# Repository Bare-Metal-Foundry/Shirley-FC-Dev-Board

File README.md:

<!--
This project follows atomic documentation.
Each subsystem is documented independently.
All configs are stored in YAML.
-->

# Shirley - Flight Controller Development Board

Shirley is high-performance flight controller hardware platform built around the STM32H743 microcontroller, designed for custom firmware development and compatibility with existing flight stacks.

## Features

### Core Hardware
- **MCU**: STM32H743ZIT6 (480 MHz Cortex-M7, FPU, DSP)
- **IMU**: ICM-40609-D (6-axis, low-noise, up to 32 kHz ODR)
- **Magnetometer**: MMC5983MA (18-bit precision with degaussing)
- **Barometer**: BMP390 High-precision altitude sensing
- **Storage**: SD card socket for flight data logging

### Power System
- **Input**: 5V via standard Pixhawk power module
- **Architecture**: 5V MUX + Dual 3.3V rails (digital + filtered analog) for low-noise sensor operation
- **Protection**: ESD protection on USB-C and power connector

### Connectivity
- **Motor Control**: 4x ESC outputs
- **RC Input**: Standard RC receiver connection
- **GPS**: Dedicated UART interface
- **Telemetry**: Bidirectional radio module support
- **USB**: Full-speed OTG for configuration and debugging
- **CAN**: FDCAN interface (in the GPS connector)
- **Debug**: Tag-Connect SWD/SWO interface

Note: All connectors are GH1.25 connectors

## Documentation

This project uses atomic documentation - each subsystem is documented independently in `/docs`:

- **[Hardware Overview](docs/hardware/overview.md)** - System architecture and block diagrams
- **[Power Architecture](docs/hardware/power-architecture.md)** - Power rail design and specifications
- **[Design Decisions](docs/hardware/design-decisions.md)** - Component selection rationale
- **[STM32 Subsystem](docs/hardware/stm32-subsystem/)** - MCU peripheral configuration

All hardware configurations are defined in machine-readable YAML format in `/config`:
- **[pinout.yaml](config/pinout.yaml)** - Complete STM32H743 pin assignments
- **[power.yaml](config/power.yaml)** - Power rail specifications and architecture

## Repository Structure

```
├── hardware/KiCad/FC_v1.0/         # KiCad 9.0 schematics and PCB layout
├── firmware/STM32 Cube IDE/        # STM32CubeMX configuration
├── config/                         # YAML configuration files
├── docs/                           # Atomic documentation by subsystem
├── docs/hardware/exports/          # exports and version history
└── resources/datasheets/           # Component datasheets organized by type
```

## Getting Started

### Overview
1. Exported schematics and renders can be found here: `exports/`
2. The different versions designed and produced are detailed here: `exports/versions-history.md`
3. An overview of the design can be found here: `docs/hardware/overview.md`

### Hardware Design
1. Open schematics in **KiCad 9.0**: `hardware/KiCad/FC_v1.0/FC-proto.kicad_sch`
2. Review hierarchical subsystem sheets (power, interfaces, sensors)
3. Custom component footprints are in `hardware/cad-layout/`

### Firmware Development
1. Open STM32CubeMX project: `firmware/STM32 Cube IDE/FC-proto-El.ioc`
2. Pin assignments match `config/pinout.yaml`
3. Connect debugger via Tag-Connect cable (SWD: PA13/PA14, SWO: PB3)

## Design Philosophy

This first revision prototype prioritizes:
- **Development-friendly**: Easy debugging via Tag-Connect, USB, and comprehensive logging
- **Compact Board**: Compact board to fit in smaller frames
- **Signal quality**: Low-noise analog power domain for sensor accuracy
- **Integration**: Integration with existing pixhawk drone hardware

## Flight Stack Compatibility

The hardware pinout and peripheral configuration supports:
- **PX4** - Full feature compatibility
- **Ardupilot** - Standard Pixhawk interface support
- **Betaflight** - High-rate control loop capability

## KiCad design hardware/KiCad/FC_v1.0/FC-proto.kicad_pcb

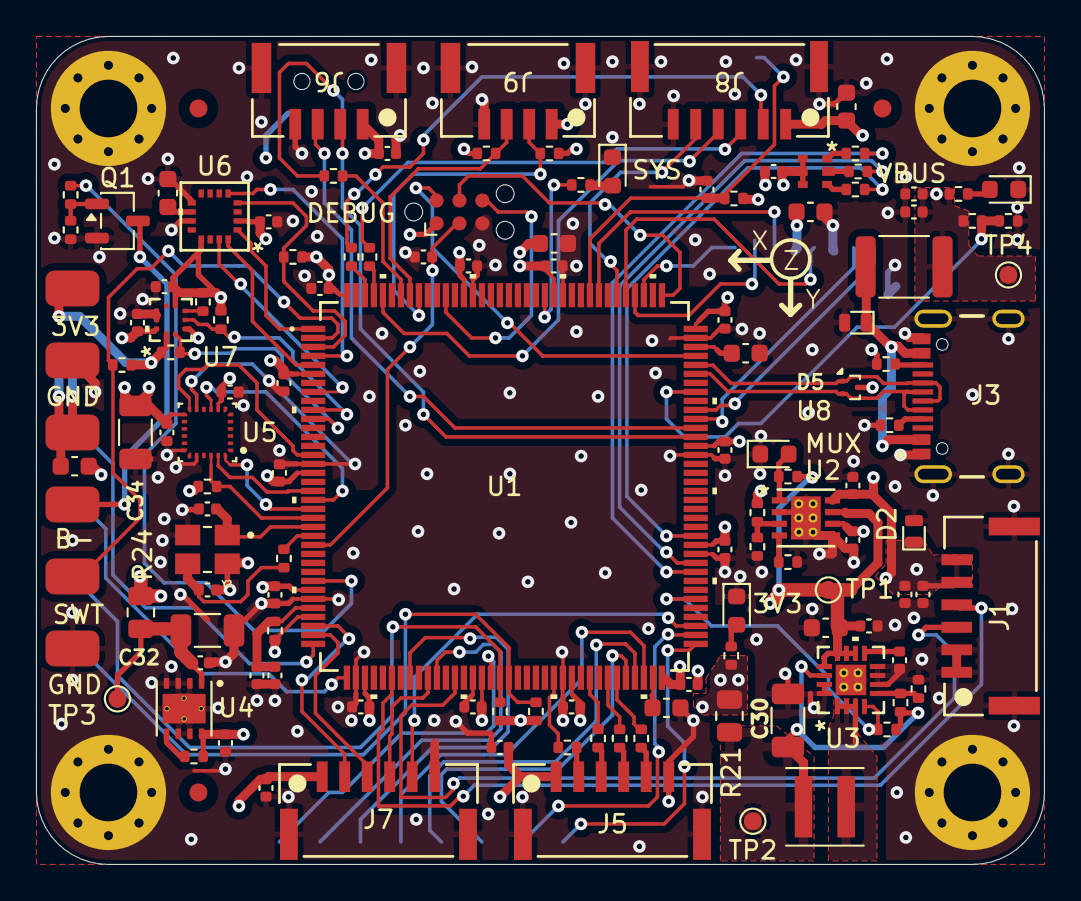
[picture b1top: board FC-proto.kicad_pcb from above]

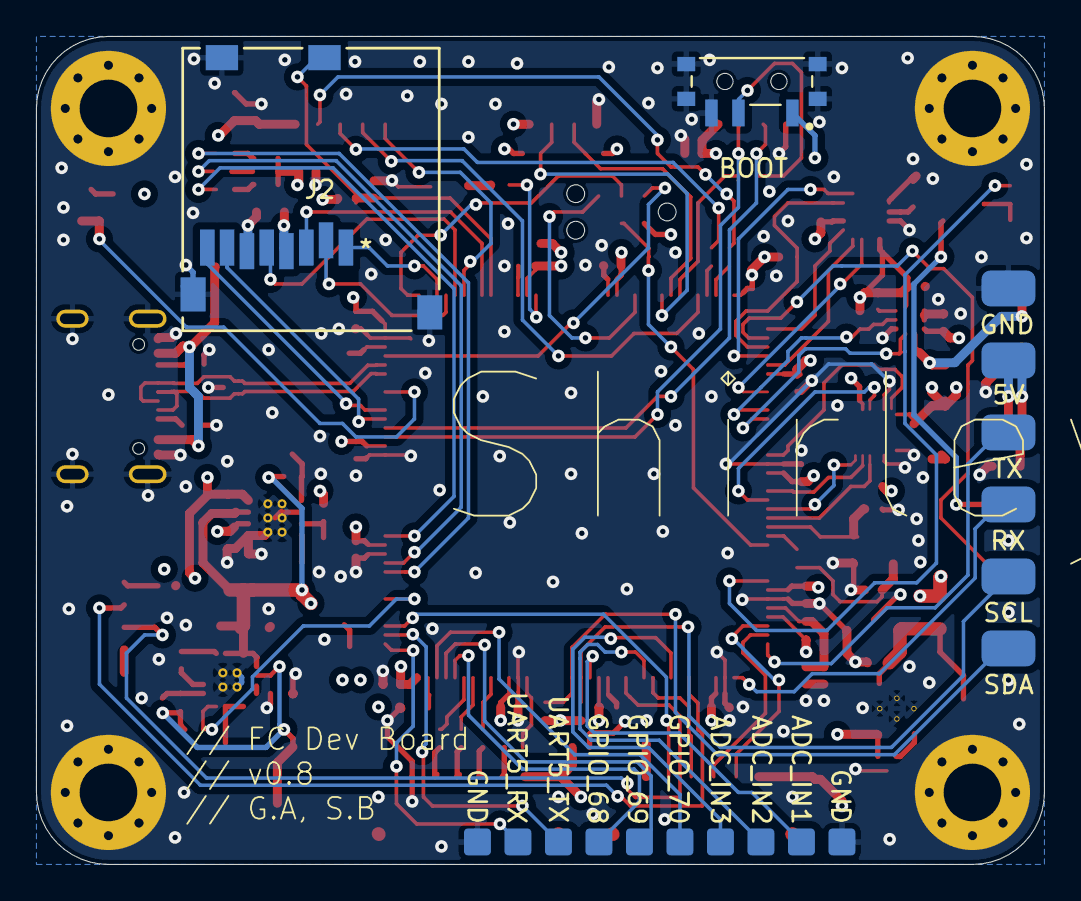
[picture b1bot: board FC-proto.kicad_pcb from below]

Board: 4 copper layers, 56.0 x 46.0 mm, 135 parts (5 on the bottom side), 105 nets.

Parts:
C1, C27, C38, C41, C48, C49: 10u; C_0603_1608Metric
C2, C3, C4, C5, C6, C7, C8, C9, C10, C11, C12, C13, C14, C15, C17, C22, C24, C25, C26, C28, C33, C35, C39, C40, C42, C44: 100n; C_0402_1005Metric
C16, C23, C31, C37, C43, C45, C46, C47: 1u; C_0402_1005Metric
C18, C19: 10p; C_0402_1005Metric
C20, C21: 2.2u; C_0603_1608Metric
C29: 3.3n; C_0402_1005Metric
C30: 22u; C_1206_3216Metric
C32: 10u; C_1206_3216Metric
C34: 2.2u; C_1206_3216Metric
C36: 10n; C_0402_1005Metric
D1: SYS_LED; LED_0603_1608Metric
D2, D5: LTVS16H5; DFN1610-2
D3: MUX_LED; LED_0603_1608Metric
D4: PWR_LED; LED_0603_1608Metric
D6: USB_LED; LED_0603_1608Metric
F1: MF-MSMF050-2; Fuse_1812_4532Metric
FID1, FID2, FID3: Fiducial; Fiducial_1mm_Mask2mm
J1, J5, J7, J8: SM06B-GHS-TB; CONN_SM06B-GHS-TB_JST
J2: MEM2061-01-188-00-A; MEM2061-01-188-00-A_GCT
J3: USB4105-GF-A; GCT_USB4105-GF-A
J4: Conn_ARM_SWD_TagConnect_TC2030-NL; Tag-Connect_TC2030-IDC-NL_2x03_P1.27mm_Vertical
J6, J9: SM04B-GHS-TB; CONN_SM04B-GHS-TB_JST
J10, J11: PAD_OUT; Pad_out_1x6
J12, J13: Conn_01x05; Pad_out_mini_1x5
L1: 2.2u; L_Coilcraft_XxL4020
LED1: 19-337C/RSBHGHC-A88/4T; SMD-B_19-337C_EVE
MH1, MH2, MH3, MH4: M3; MountingHole_3.2mm_M3_Pad_Via
Q1: AO3400A; SOT-23-3
R1, R23, R25, R26, R29, R37, R42: 10k; R_0402_1005Metric
R2: 47; R_0402_1005Metric
R3: 0R; R_0402_1005Metric
R4: 100; R_0402_1005Metric
R5, R6, R7, R8, R9, R10: 33; R_0402_1005Metric
R11, R12, R13: 220; R_0402_1005Metric
R14: 4.3k; R_0402_1005Metric
R15: 820; R_0402_1005Metric
R16, R17, R33: 250; R_0402_1005Metric
R18: 100k; R_0402_1005Metric
R19: 7.5k; R_0402_1005Metric
R20: 2.4k; R_0402_1005Metric
R21, R24: 0R; R_0805_2012Metric
R22: 1.5k; R_0402_1005Metric
R27, R28: 2.2k; R_0402_1005Metric
R30: 56k; R_0402_1005Metric
R31: 43k; R_0402_1005Metric
R32: 82k; R_0402_1005Metric
R34, R35: 5.1k; R_0402_1005Metric
R36: 1k; R_0402_1005Metric
R38, R39, R40, R41: 4.7k; R_0402_1005Metric
SW1: PCM12SMTRFC; SW_PCM12SMTR
TP1, TP2, TP3, TP4: TestPoint; TestPoint_Pad_D1.0mm
U1: STM32H743ZIT6
U2: TPS2113ADRBR; TPS2113A
U3: TPS62130ARGTR
U4: TPS7A2133PQWDRBRQ1
U5: ICM-40609-D
U6: MMC5983MA
U7: BMP390
U8: TPD2EUSB30A; Texas_DRT-3
Y2: 16MHz; TSX-3225_16MHz

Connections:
+3.3V: C1.1, C2.1, C3.1, C4.1, C5.1, C6.1, C7.1, C8.1, C9.1, C10.1, C11.1, C12.1, C13.1, C14.1, C22.1, C36.1, C40.1, C41.1, J2.P4 (VDD), J4.1 (VCC), J11.1, LED1.2, LED1.4, LED1.6, R21.1, R22.2, R25.2, R26.2, R27.2, R28.2, R29.2, R30.2, R38.2, R39.2, R40.2, R41.2, R42.2, SW1.1 (A), U1.6 (VBAT), U1.17 (VDD), U1.30 (VDD), U1.39 (VDD), U1.52 (VDD), U1.62 (VDD), U1.72 (VDD), U1.84 (VDD), U1.95 (VDD33_USB), U1.108 (VDD), U1.121 (VDD), U1.131 (VDD), U1.144 (VDD), U5.8 (VDDIO), U6.13 (VDDIO), U7.1 (VDDIO), U7.6 (CSB)
+3.3VA: C34.2, C35.2, C37.1, C39.1, R2.1, R24.1, U1.33 (VDDA), U5.13 (VDD), U6.2 (VDD), U7.10 (VDD)
+5V: C23.1, C24.1, C25.1, C45.1, C46.1, C47.1, C48.1, C49.2, D2.1 (K), J1.5, J1.6, J5.1, J6.1, J7.1, J8.1, J9.1, J10.2, J11.3, R14.2, U2.8 (IN1)
+5V_SYS: C27.2, C28.2, C31.2, R17.1, R23.2, TP1.1, U2.7 (OUT), U3.10 (VIN), U3.11 (VIN), U3.12 (VIN), U3.13 (EN), U4.8 (IN)
/BOOT0: R1.2, U1.138 (BOOT0)
/LED_B_K: LED1.5, R13.2
/LED_G_K: LED1.3, R12.2
/LED_R_K: LED1.1, R11.2
/Power Section/Buck_Out: C30.2, L1.2, R18.2, R19.2, R21.2, TP2.1, U3.14 (VOS)
/Power Section/SW_L: L1.1, U3.1 (SW), U3.2 (SW), U3.3 (SW)
/Power Section/sw_status: D3.2 (A), R17.2, U2.1 (STAT)
/SW_BOOT0: R1.1, SW1.2 (B)
ADC_IN1: J13.4, U1.53 (PF13)
ADC_IN2: J13.2, U1.44 (PC4)
ADC_IN3: J13.3, U1.47 (PB1)
BAR_SCL: R28.1, U1.11 (PF1), U7.2 (SCK)
BAR_SDA: R27.1, U1.10 (PF0), U7.4 (SDI)
BAT_CURRENT: J1.4, U1.42 (PA6)
BAT_VOLTAGE: J1.3, U1.49 (PF11)
BUZZ: R36.2, U1.29 (PC3_C)
BUZZER-: J11.4, Q1.3 (D)
DEBUG_NRST: C15.1, J4.3 (~RESET), U1.25 (NRST)
DEBUG_SWCLK: J4.4 (SWCLK), U1.109 (PA14)
DEBUG_SWDIO: J4.2 (SWDIO), U1.105 (PA13)
DEBUG_SWO: J4.6 (SWO), U1.133 (PB3)
ESC_PWM1: J5.2, R7.1
ESC_PWM2: J5.3, R8.1
ESC_PWM3: J5.4, R9.1
ESC_PWM4: J5.5, R10.1
GND: C1.2, C2.2, C3.2, C4.2, C5.2, C6.2, C7.2, C8.2, C9.2, C10.2, C11.2, C12.2, C13.2, C14.2, C15.2, C16.2, C17.2, C18.2, C19.2, C20.2, C21.2, C22.2, C23.2, C24.2, C25.2, C26.1, C27.1, C28.1, C29.2, C30.1, C31.1, C32.1, C33.1, C34.1, C35.1, C36.2, C37.2, C38.2, C39.2, C40.2, C41.2, C42.1, C43.2, C44.2, C45.2, C46.2, C47.2, C48.2, C49.1, D1.1 (K), D2.2 (A), D3.1 (K), D4.1 (K), D5.2 (A), D6.1 (K), J1.1, J1.2, J1.7 (SHIELD), J1.8 (SHIELD), J2.9 (CARD_DETECT), J2.11 (GND), J2.12 (GND), J2.P6 (VSS), J3.A1 (GND), J3.B1 (GND), J3.SH1 (SHIELD), J3.SH2 (SHIELD), J3.SH3 (SHIELD), J3.SH4 (SHIELD), J4.5 (GND), J5.6, J5.7 (SHIELD), J5.8 (SHIELD), J6.4, J6.5 (SHIELD), J6.6 (SHIELD), J7.6, J7.7 (SHIELD), J7.8 (SHIELD), J8.6, J8.7 (SHIELD), J8.8 (SHIELD), J9.4, J9.5 (SHIELD), J9.6 (SHIELD), J10.1, J11.2, J11.6, J12.1, J13.5, MH1.1, MH2.1, MH3.1, MH4.1, Q1.2 (S), R15.1, R16.1, R20.1, R32.1, R34.1, R35.1, R37.1, SW1.3 (A), SW1.S1 (SHIELD), SW1.S2 (SHIELD), SW1.S3 (SHIELD), SW1.S4 (SHIELD), U1.16 (VSS), U1.31 (VSSA), U1.38 (VSS), U1.51 (VSS), U1.61 (VSS), U1.83 (VSS), U1.94 (VSS), U1.107 (VSS), U1.120 (VSS), U1.130 (VSS), U2.2 (EN_), U2.5 (GND), U2.9 (GND), U3.6 (GND), U3.7 (FSW), U3.8 (DEF), U3.15 (GND), U3.16 (GND), U3.17 (GND), U4.2 (NC), U4.3 (NC), U4.4 (GND), U4.6 (NC), U4.7 (NC), U4.9 (GND), U5.11 (RESV), U5.18 (GND), U5.20 (RESV), U6.9 (GND), U6.11 (GND), U7.3 (VSS), U7.8 (VSS), U7.9 (VSS), U8.3 (GND), Y2.2, Y2.4
GPIO_68: J12.4, U1.68 (PE15)
GPIO_69: J12.5, U1.69 (PB10)
GPIO_70: J13.1, U1.70 (PB11)
GPS_CAN_RX: J8.5, U1.114 (PD0)
GPS_CAN_TX: J8.4, U1.140 (PB9)
GPS_RX: J8.3, R5.2
GPS_TX: J8.2, R6.2
HSE_IN: C18.1, U1.23 (PH0), Y2.1
HSE_OUT: R3.1, U1.24 (PH1)
I2C_SCL: J9.2, R39.1, U1.136 (PB6)
I2C_SDA: J9.3, R38.1, U1.137 (PB7)
IMU_CS: R25.1, U1.22 (PF10), U5.22 (CS)
IMU_INT: U1.15 (PF5), U5.12 (INT1/INT)
IMU_MISO: U1.20 (PF8), U5.9 (SDO/AD0)
IMU_MOSI: U1.21 (PF9), U5.24 (SDA/SDI/SDIO)
IMU_SCK: U1.19 (PF7), U5.23 (SCL/SCLK)
MAG_CS: R26.1, U1.3 (PE4), U6.4 (SPI_CS)
MAG_INT: U1.8 (PC14), U6.15 (INT)
MAG_MISO: U1.4 (PE5), U6.5 (SPI_SDO)
MAG_MOSI: U1.5 (PE6), U6.16 (SDA/SPI_SDI)
MAG_SCK: U1.1 (PE2), U6.1 (SCL/SPI_SCK)
unnamed: C19.1, R3.2, Y2.3
unnamed: C20.1, U1.71 (VCAP)
unnamed: C21.1, U1.106 (VCAP)
unnamed: D1.2 (A), R4.2
unnamed: D4.2 (A), R22.1
unnamed: D5.1 (K), F1.2, J3.A4 (VBUS), J3.B4 (VBUS)
unnamed: D6.2 (A), R33.1
unnamed: J3.A5 (CC1), R34.2
unnamed: J3.B5 (CC2), R35.2
unnamed: Q1.1 (G), R36.1, R37.2
unnamed: R4.1, U1.122 (PD6)
unnamed: R5.1, U1.141 (PE0)
unnamed: R6.1, U1.142 (PE1)
unnamed: R7.2, U1.60 (PE9)
unnamed: R8.2, U1.64 (PE11)
unnamed: R9.2, U1.66 (PE13)
unnamed: R10.2, U1.67 (PE14)
unnamed: R16.2, U2.4 (ILIM)
unnamed: R14.1, R15.2, U2.3 (VSNS)
unnamed: R19.1, R20.2, U3.5 (FB)
unnamed: C29.1, U3.9 (SS/TR)
unnamed: R23.1, U4.5 (EN)
unnamed: C32.2, C33.2, R24.2, TP3.1, U4.1 (OUT)
unnamed: C38.1, U6.10 (CAP)
unnamed: R29.1, U7.5 (SDO)
PO_RX: J10.4, U1.37 (PA3)
PO_SCL: J10.5, R41.1, U1.54 (PF14)
PO_SDA: J10.6, R40.1, U1.55 (PF15)
PO_TX: J10.3, U1.36 (PA2)
PWR_GOOD: R18.1, U1.78 (PD9), U3.4 (PG)
RC_RX: J6.3, U1.97 (PC7)
RC_TX: J6.2, U1.96 (PC6)
RGB_LED_B: R13.1, U1.85 (PD14)
RGB_LED_G: R12.1, U1.82 (PD13)
RGB_LED_R: R11.1, U1.81 (PD12)
SD_CDS: C42.2, J2.10 (CARD_DETECT), R30.1, U1.117 (PD3)
SD_CLK: J2.P5 (CLK), U1.113 (PC12)
SD_CMD: J2.P3 (CMD), U1.116 (PD2)
SD_DAT0: J2.P7 (DAT0), U1.98 (PC8)
SD_DAT1: J2.P8 (DAT1), U1.99 (PC9)
SD_DAT2: J2.P1 (DAT2), U1.111 (PC10)
SD_DAT3: J2.P2 (DAT3/CD), U1.112 (PC11)
SWITCH: J11.5, R42.1, U1.2 (PE3)
TELEM_CTS: J7.4, U1.46 (PB0)
TELEM_RTS: J7.5, U1.75 (PB14)
TELEM_RX: J7.3, U1.35 (PA1)
TELEM_TX: J7.2, U1.34 (PA0)
UART5_RX: J12.2, U1.73 (PB12)
UART5_TX: J12.3, U1.74 (PB13)
USB_D+: J3.A6 (D1+), J3.B6 (D2+), U1.104 (PA12), U8.1 (D+)
USB_D-: J3.A7 (D1-), J3.B7 (D2-), U1.103 (PA11), U8.2 (D-)
USB_VBUS_SENSE: R31.1, R32.2, U1.101 (PA9)
VBUS: C26.2, C43.1, C44.1, F1.1, R31.2, R33.2, TP4.1, U2.6 (IN2)
VREF+_MCU: C16.1, C17.1, R2.2, U1.32 (VREF+)

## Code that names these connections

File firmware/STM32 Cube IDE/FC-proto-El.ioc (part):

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Mcu.Name=STM32H743ZITx
Mcu.Package=LQFP144
Mcu.UserName=STM32H743ZITx
PA0.Mode=Asynchronous
PA0.Signal=UART4_TX
PA1.Mode=Asynchronous
PA1.Signal=UART4_RX
PA11.Mode=Device_Only
PA11.Signal=USB_OTG_FS_DM
PA12.Mode=Device_Only
PA12.Signal=USB_OTG_FS_DP
PA13\ (JTMS/SWDIO).Mode=Trace_Asynchronous_SW
PA13\ (JTMS/SWDIO).Signal=DEBUG_JTMS-SWDIO
PA14\ (JTCK/SWCLK).Mode=Trace_Asynchronous_SW
PA14\ (JTCK/SWCLK).Signal=DEBUG_JTCK-SWCLK
PA2.Mode=Asynchronous
PA2.Signal=USART2_TX
PA3.Mode=Asynchronous
PA3.Signal=USART2_RX
PA6.Signal=ADCx_INP3
PA9.Mode=Activate_VBUS
PA9.Signal=USB_OTG_FS_VBUS
PB0.Mode=CTS_RTS
PB0.Signal=UART4_CTS
PB1.Signal=ADCx_INP5
PB10.Signal=GPIO_Output
PB11.Signal=GPIO_Output
PB12.Mode=Asynchronous
PB12.Signal=UART5_RX
PB13.Mode=Asynchronous
PB13.Signal=UART5_TX
PB14.Mode=CTS_RTS
PB14.Signal=UART4_RTS
PB3\ (JTDO/TRACESWO).Mode=Trace_Asynchronous_SW
PB3\ (JTDO/TRACESWO).Signal=DEBUG_JTDO-SWO
PB6.Mode=I2C
PB6.Signal=I2C1_SCL
PB7.Mode=I2C
PB7.Signal=I2C1_SDA
PB9.Mode=FDCAN_Activate
PB9.Signal=FDCAN1_TX
PC10.Mode=SD_4_bits_Wide_bus
PC10.Signal=SDMMC1_D2
PC11.Mode=SD_4_bits_Wide_bus
PC11.Signal=SDMMC1_D3
PC12.Mode=SD_4_bits_Wide_bus
PC12.Signal=SDMMC1_CK
PC14-OSC32_IN\ (OSC32_IN).Signal=GPXTI14
PC3_C.Signal=GPIO_Output
PC4.Signal=ADCx_INP4
PC6.Mode=Asynchronous
PC6.Signal=USART6_TX
PC7.Mode=Asynchronous
PC7.Signal=USART6_RX
PC8.Mode=SD_4_bits_Wide_bus
PC8.Signal=SDMMC1_D0
PC9.Mode=SD_4_bits_Wide_bus
PC9.Signal=SDMMC1_D1
PD0.Mode=FDCAN_Activate
PD0.Signal=FDCAN1_RX
PD12.Signal=S_TIM4_CH1
PD13.Signal=S_TIM4_CH2
PD14.Signal=S_TIM4_CH3
PD2.Mode=SD_4_bits_Wide_bus
PD2.Signal=SDMMC1_CMD
PD3.Signal=GPIO_Input
PD6.Signal=GPIO_Output
PD9.Signal=GPIO_Input
PE0.Mode=Asynchronous
PE0.Signal=UART8_RX
PE1.Mode=Asynchronous
PE1.Signal=UART8_TX
PE11.Signal=S_TIM1_CH2
PE13.Signal=S_TIM1_CH3
PE14.Signal=S_TIM1_CH4
PE15.Signal=GPIO_Output
PE2.Mode=Full_Duplex_Master
PE2.Signal=SPI4_SCK
PE3.Signal=GPIO_Input
PE4.Signal=GPIO_Output
PE5.Mode=Full_Duplex_Master
PE5.Signal=SPI4_MISO
PE6.Mode=Full_Duplex_Master
PE6.Signal=SPI4_MOSI
PE9.Signal=S_TIM1_CH1
PF0.Mode=I2C
PF0.Signal=I2C2_SDA
PF1.Mode=I2C
PF1.Signal=I2C2_SCL
PF10.Signal=GPIO_Output
PF11.Mode=IN2-Single-Ended
PF11.Signal=ADC1_INP2
PF13.Mode=IN2-Single-Ended
PF13.Signal=ADC2_INP2
PF14.Mode=I2C
PF14.Signal=I2C4_SCL
PF15.Mode=I2C
PF15.Signal=I2C4_SDA
PF5.Signal=GPXTI5
PF7.Mode=Full_Duplex_Master
PF7.Signal=SPI5_SCK
PF8.Mode=Full_Duplex_Master
PF8.Signal=SPI5_MISO
PF9.Mode=Full_Duplex_Master
PF9.Signal=SPI5_MOSI
PH0-OSC_IN\ (PH0).Mode=HSE-External-Oscillator
PH0-OSC_IN\ (PH0).Signal=RCC_OSC_IN
PH1-OSC_OUT\ (PH1).Mode=HSE-External-Oscillator
PH1-OSC_OUT\ (PH1).Signal=RCC_OSC_OUT
RCC.SYSCLKFreq_VALUE=64000000
board=custom

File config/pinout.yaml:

# Pinout configuration of the STM32H743ZIT6 MCU
# This file maps the various peripherals to their corresponding GPIO pins.

# Typycal descripton structure:
# stm32<MCU_MODEL>:
#   <PERIPHERAL_NAME>:  # <PERIPHERAL_DESCRIPTION>
#     <SIGNAL_NAME>: <PIN_NAME> (<PIN_COMMENT>)
#     ... 

# Matching v0.7 board as of 2025-01-04

stm32h743ZIT6:
  uart4:  #Telemetry
    tx:  PA0
    rx:  PA1
    cts: PB0
    rts: PB14

  uart5:  #Mini Pad Out UART
    tx: PB13
    rx: PB12

  uart8:    #GPS
    tx: PE1
    rx: PE0

  usart2:   #Pad Out USART
    tx: PA2
    rx: PA3

  usart6:   #RC Receiver
    tx: PC6
    rx: PC7

  spi4:   #Magnometer
    sck:  PE2
    miso: PE5
    mosi: PE6

  spi5:   #IMU
    sck:  PF7
    miso: PF8
    mosi: PF9

  i2c1:   #I2C Connector (ex: External Compass)
    sda: PB7
    scl: PB6

  i2c2:   #Barometer
    sda: PF0
    scl: PF1

  i2c4:    #Pad Out I2C
    sda: PF15
    scl: PF14

  fdcan1:   #GPS CAN Bus
    rx: PD0
    tx: PB9

  adc1:   #Battery Voltage/Current Sensor
    inp2: PF11   # ADC1_INP2 Voltage Sensor
    inp3: PA6    # ADCx_INP3 Current Sensor

  adc2:   #Pad Out ADCs 
    inp2: PF13   # ADC2_INP2
    inp4: PC4    # ADCx_INP4
    inp5: PB1    # ADCx_INP5

  tim1:  #Motors ESC PWM/DShot
    ch1: PE9    # S_TIM1_CH1 (PWM)
    ch2: PE11   # S_TIM1_CH2 (PWM)
    ch3: PE13   # S_TIM1_CH3 (PWM)
    ch4: PE14   # S_TIM1_CH4 (PWM)

  tim4:   #RGB LED
    ch1: PD12   # S_TIM4_CH1 (PWM) Red Channel
    ch2: PD13   # S_TIM4_CH2 (PWM) Green Channel
    ch3: PD14   # S_TIM4_CH3 (PWM) Blue Channel

  sdmmc1:   #SD Card
    d0:  PC8
    d1:  PC9
    d2:  PC10
    d3:  PC11
    ck:  PC12
    cmd: PD2
    cds: PD3  # Card Detect Switch

  usb_otg_fs:   #USB-C
    dm:   PA11
    dp:   PA12
    vbus: PA9

  sys_led:    #System Status LED
    pin: PD6

  ext_switch:   #External System Switch
    pin: PE3

  pwr_good:     #Power Good Signal (Buck 3V3 rail)
    pin: PD9

  buzzer:    #External Active Buzzer
    pin: PC3_C

  external_gpios:   #Pad Out GPIOs
    pin1: PE15  #GPIO_68
    pin2: PB10  #GPIO_69
    pin3: PB11  #GPIO_70

  debug:    #SWD Programming/Debugging Tag Conector
    swdio: "PA13 (JTMS/SWDIO)"
    swclk: "PA14 (JTCK/SWCLK)"
    swo:   "PB3 (JTDO/TRACESWO)"

  hse:    #Crystal Oscillator
    osc_in:  "PH0-OSC_IN (PH0)"
    osc_out: "PH1-OSC_OUT (PH1)"

  system:
    systick:    VP_SYS_VS_Systick
    memorymap:  VP_MEMORYMAP_VS_MEMORYMAP
    tim1_clock: VP_TIM1_VS_ClockSourceINT
    tim4_clock: VP_TIM4_VS_ClockSourceINT

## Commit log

2025-12-01 Schematic Upgrade
2025-12-03 FC design 0.3
2025-12-08 FC design 0.4
2025-12-10 FC design v0.5
2025-12-10 FC design v0.5 corrected
2025-12-16 Complete Routing
2025-12-16 Backup_files
2025-12-17 Top/Bot pours
2025-12-18 Silkscreen improvements
2025-12-23 Silkscreen Finish
2025-12-23 Silkscreen Finish*
2026-01-03 Pinout / DRC check
2026-01-04 pinout description v0.7 update
2026-01-04 power config improved
2026-01-09 adding version history
2026-01-11 adding hardware overview
2026-01-14 top layer picture update
2026-01-14 repo cleaning
2026-01-18 changing USB ESD IC (v0.8)
2026-02-22 Component library update
2026-02-25 Component library fully complete
2026-02-25 Schematic update v0.9
2026-03-11 manufacturing exports v0.9
2026-03-13 Pressure sensor replacement
2026-03-21 Manufacturing v0.9.5
2026-03-22 repo cleanup
2026-05-05 First_version_manufactured
2026-05-05 Update_pres_pic
